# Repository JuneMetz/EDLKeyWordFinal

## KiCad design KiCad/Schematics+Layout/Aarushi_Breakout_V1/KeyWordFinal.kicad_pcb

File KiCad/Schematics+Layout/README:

Main Board Version 1 (MCP1642 Op AMP)

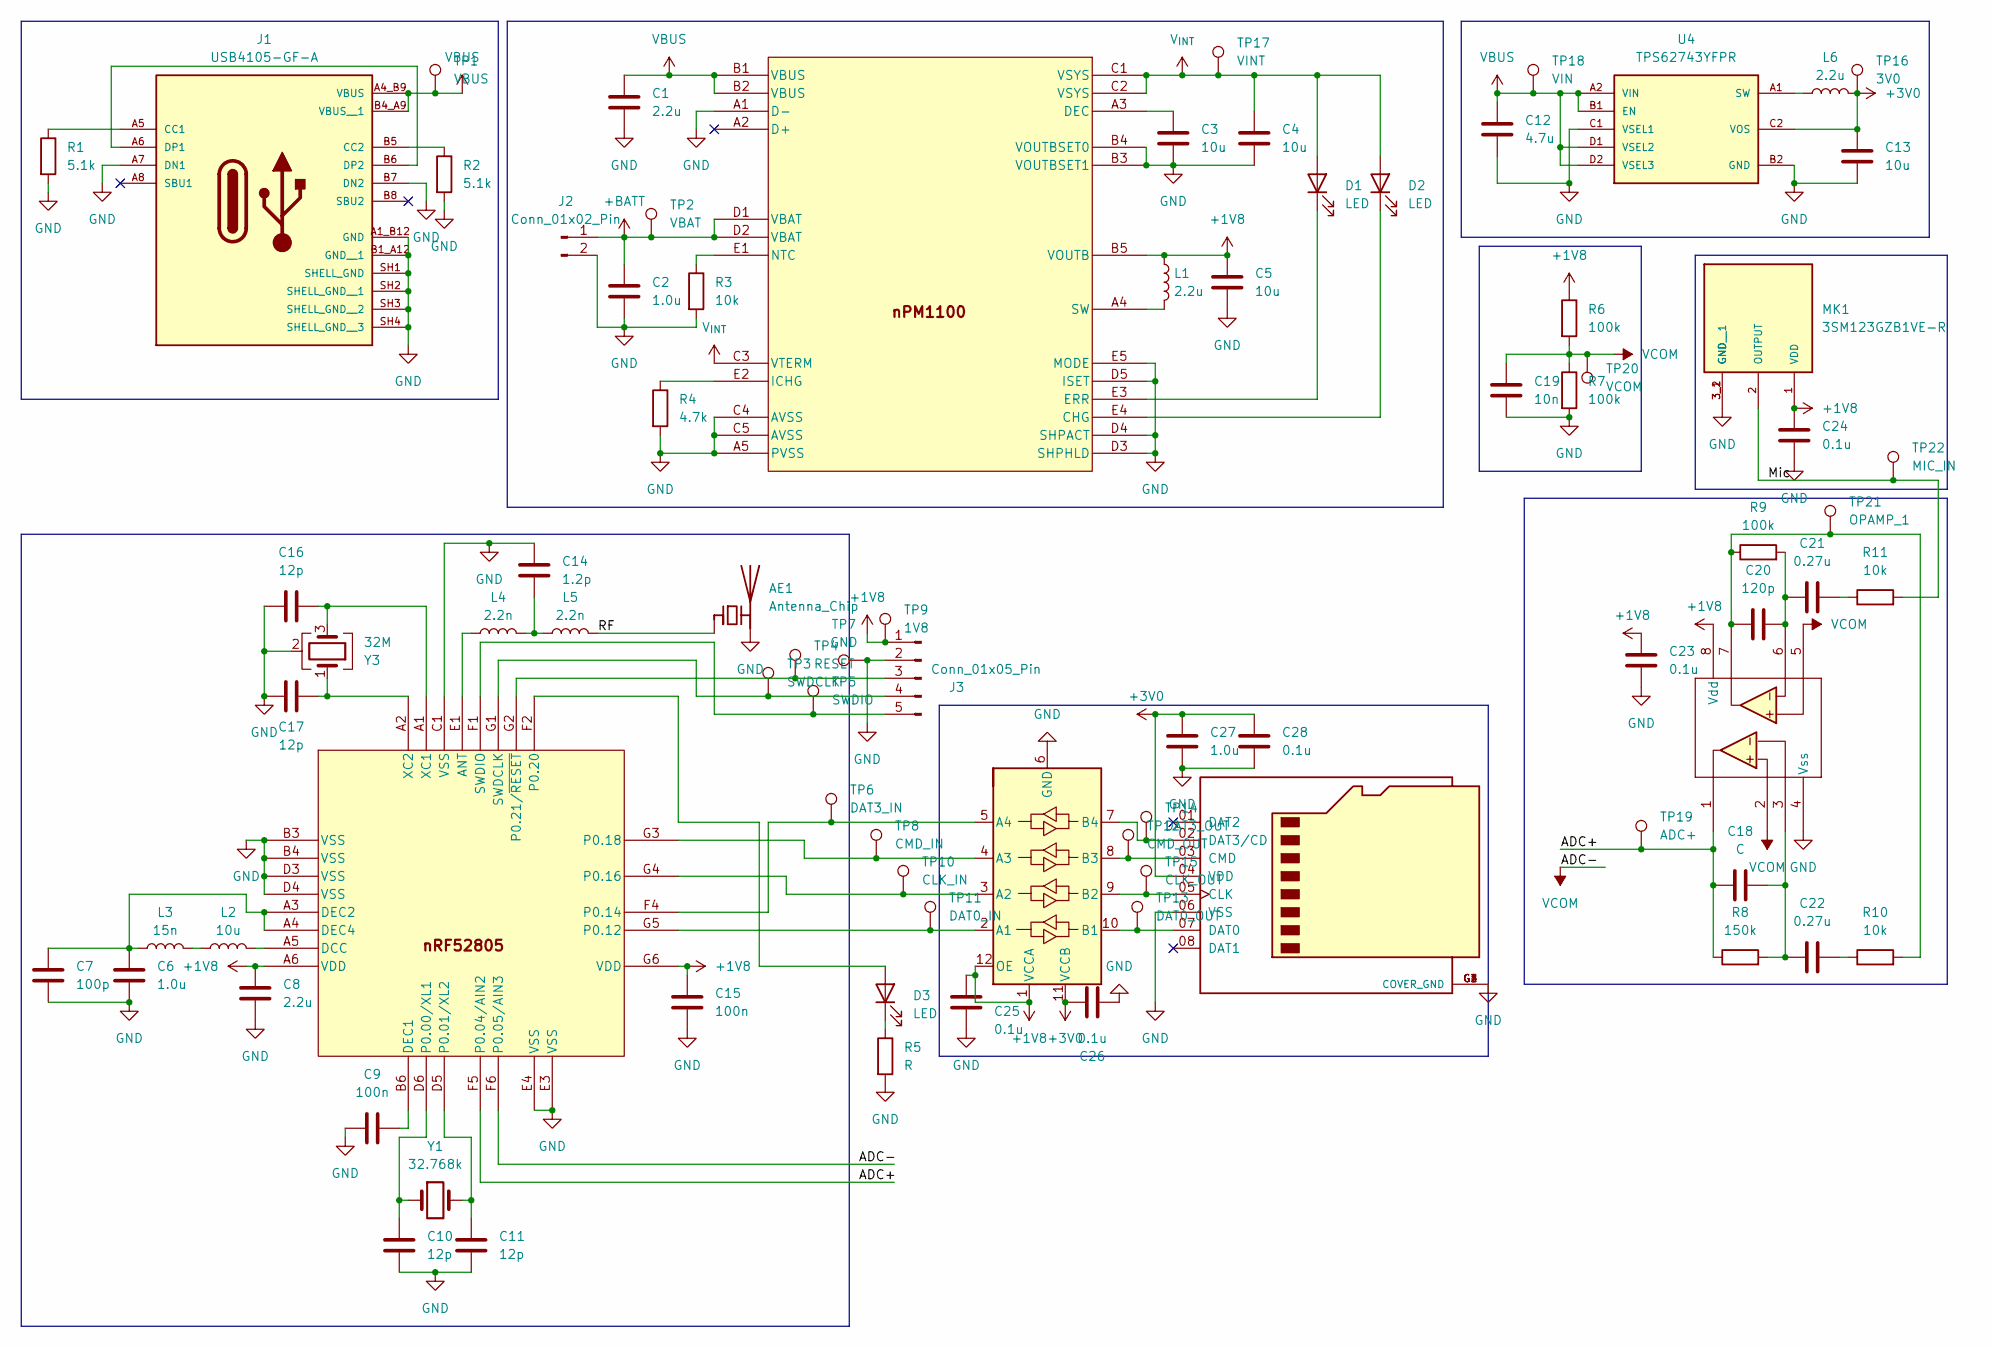
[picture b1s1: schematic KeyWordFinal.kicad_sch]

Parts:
AE1: Antenna_Chip; Texas_SWRA117D_2.4GHz_Left
C1: 2.2u; C_0603_1608Metric
C2: 1.0u; C_0201_0603Metric
C3, C4, C5, C13: 10u; C_0603_1608Metric
C6: 1.0u; C_0402_1005Metric
C7: 100p; C_0201_0603Metric
C8: 2.2u; C_0402_1005Metric
C9, C15: 100n; C_0201_0603Metric
C10, C11, C16, C17: 12p; C_0201_0603Metric
C12: 4.7u; C_0603_1608Metric
C14: 1.2p; C_0201_0603Metric
C18: C; C_0603_1608Metric
C19: 10n; C_0603_1608Metric
C20: 120p; C_0603_1608Metric
C21, C22: 0.27u; C_0603_1608Metric
C23, C24, C25, C26, C28: 0.1u; C_0603_1608Metric
C27: 1.0u; C_0603_1608Metric
D1, D2, D3: LED; LED_0603_1608Metric
J1: USB4105-GF-A; USB4105; PARTREV B4
J2: Conn_01x02_Pin; PinSocket_1x02_P2.54mm_Vertical
J3: Conn_01x05_Pin; PinSocket_1x05_P2.54mm_Vertical
J4: MSD-10-C; PARTREV 1.0
L1, L6: 2.2u; L_0805_2012Metric
L2: 10u; L_0603_1608Metric
L3: 15n; L_0402_1005Metric
L4, L5: 2.2n; L_0201_0603Metric
MK1: 3SM123GZB1VE-R; MIC_3SM123GZB1VE-R; PARTREV 1.4
R1, R2: 5.1k; R_0201_0603Metric
R3: 10k; R_0201_0603Metric
R4: 4.7k; R_0201_0603Metric
R5: R; R_0402_1005Metric
R6: 100k; R_0603_1608Metric
R7, R9: 100k; R_0402_1005Metric
R8: 150k; R_0402_1005Metric
R10, R11: 10k; R_0402_1005Metric
TP1: VBUS; TestPoint_Loop_D1.80mm_Drill1.0mm_Beaded
TP2: VBAT; TestPoint_Loop_D1.80mm_Drill1.0mm_Beaded
TP3: SWDCLK; TestPoint_Loop_D1.80mm_Drill1.0mm_Beaded
TP4: RESET; TestPoint_Loop_D1.80mm_Drill1.0mm_Beaded
TP5: SWDIO; TestPoint_Loop_D1.80mm_Drill1.0mm_Beaded
TP6: DAT3_IN; TestPoint_Loop_D1.80mm_Drill1.0mm_Beaded
TP7: GND; TestPoint_Loop_D1.80mm_Drill1.0mm_Beaded
TP8: CMD_IN; TestPoint_Loop_D1.80mm_Drill1.0mm_Beaded
TP9: 1V8; TestPoint_Loop_D1.80mm_Drill1.0mm_Beaded
TP10: CLK_IN; TestPoint_Loop_D1.80mm_Drill1.0mm_Beaded
TP11: DAT0_IN; TestPoint_Loop_D1.80mm_Drill1.0mm_Beaded
TP12: CMD_OUT; TestPoint_Loop_D1.80mm_Drill1.0mm_Beaded
TP13: DAT0_OUT; TestPoint_Loop_D1.80mm_Drill1.0mm_Beaded
TP14: DAT3_OUT; TestPoint_Loop_D1.80mm_Drill1.0mm_Beaded
TP15: CLK_OUT; TestPoint_Loop_D1.80mm_Drill1.0mm_Beaded
TP16: 3V0; TestPoint_Loop_D1.80mm_Drill1.0mm_Beaded
TP17: VINT; TestPoint_Loop_D1.80mm_Drill1.0mm_Beaded
TP18: VIN; TestPoint_Loop_D1.80mm_Drill1.0mm_Beaded
TP19: ADC+; TestPoint_Loop_D1.80mm_Drill1.0mm_Beaded
TP20: VCOM; TestPoint_Loop_D1.80mm_Drill1.0mm_Beaded
TP21: OPAMP_1; TestPoint_Loop_D1.80mm_Drill1.0mm_Beaded
TP22: MIC_IN; TestPoint_Loop_D1.80mm_Drill1.0mm_Beaded
U1: NRF52805-CAAA-R; NRF52805
U2: NPM1100-CAAA-R7; NPM1100
U3: TXB0104RUTR; TXB0104
U4: TPS62743YFPR; TPS62743
U5: MCP6142T-E/MS; MSOP-8_3x3mm_P0.65mm
Y1: 32.768k; Crystal_SMD_2012-2Pin_2.0x1.2mm
Y3: 32M; Crystal_SMD_2016-4Pin_2.0x1.6mm

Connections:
+1V8: C5.1, C8.1, C15.2, C23.2, C24.2, C25.2, J3.1, L1.1, MK1.1 (VDD), R6.1, TP9.1 (1_1), U1.A6 (VDD), U1.G6 (VDD), U2.B5 (VOUTB), U3.1 (VCCA), U3.12 (OE), U5.8 (Vdd)
+3V0: C13.1, C26.2, C27.1, C28.1, J4.04 (VDD), L6.2, TP16.1 (1_1), U3.11 (VCCB), U4.C2 (VOS)
/ADC+: C18.1, R8.1, TP19.1 (1_1), U1.F5 (P0.04/AIN2), U5.1
/Mic: MK1.2 (OUTPUT), R11.2, TP22.1 (1_1)
/RF: AE1.1 (FEED), L5.2
GND: AE1.2 (PCB_Trace), C1.2, C2.2, C3.2, C4.2, C5.2, C6.2, C7.2, C8.2, C9.1, C10.2, C11.2, C12.2, C13.2, C14.1, C15.1, C16.1, C17.1, C19.2, C23.1, C24.1, C25.1, C26.1, C27.2, C28.2, J1.A1_B12 (GND), J1.A7 (DN1), J1.B1_A12 (GND__1), J1.B7 (DN2), J1.SH1 (SHELL_GND), J1.SH2 (SHELL_GND__1), J1.SH3 (SHELL_GND__2), J1.SH4 (SHELL_GND__3), J2.2, J3.2, J4.06 (VSS), J4.G1 (COVER_GND), J4.G2 (COVER_GND), J4.G3 (COVER_GND), J4.G4 (COVER_GND), MK1.3_1 (GND), MK1.3_2 (GND__1), R1.2, R2.2, R3.2, R4.2, R5.2, R7.2, TP7.1 (1_1), U1.B3 (VSS), U1.B4 (VSS), U1.C1 (VSS), U1.D3 (VSS), U1.D4 (VSS), U1.E3 (VSS), U1.E4 (VSS), U2.A1 (D-), U2.A5 (PVSS), U2.B3 (VOUTBSET1), U2.B4 (VOUTBSET0), U2.C4 (AVSS), U2.C5 (AVSS), U2.D3 (SHPHLD), U2.D4 (SHPACT), U2.D5 (ISET), U2.E5 (MODE), U3.6 (GND), U4.B2 (GND), U4.C1 (VSEL1), U5.4 (Vss), Y3.2 (G), Y3.4 (G); also elsewhere on the board
unnamed: C14.2, L4.2, L5.1
unnamed: C18.2, C22.1, R8.2, U5.3
unnamed: C20.1, R9.1, R10.2, TP21.1 (1_1), U5.7
unnamed: C20.2, C21.1, R9.2, U5.6
unnamed: C21.2, R11.1
unnamed: C22.2, R10.1
unnamed: D1.1 (K), U2.E3 (ERR)
unnamed: D2.1 (K), U2.E4 (CHG)
unnamed: D3.2 (A), U1.F2 (P0.20)
unnamed: D3.1 (K), R5.1
unnamed: J1.A5 (CC1), R1.1
unnamed: J1.B5 (CC2), R2.1
unnamed: J1.A6 (DP1), J1.B6 (DP2)
unnamed: J3.3, TP4.1 (1_1), U1.G2 (P0.21/~RESET)
unnamed: J3.4, TP3.1 (1_1), U1.G1 (SWDCLK)
unnamed: J3.5, TP5.1 (1_1), U1.F1 (SWDIO)
unnamed: J4.05 (CLK), TP15.1 (1_1), U3.9 (B2)
unnamed: J4.03 (CMD), TP12.1 (1_1), U3.8 (B3)
unnamed: J4.07 (DAT0), TP13.1 (1_1), U3.10 (B1)
unnamed: J4.02 (DAT3/CD), TP14.1 (1_1), U3.7 (B4)
unnamed: L2.1, L3.2
unnamed: L4.1, U1.E1 (ANT)
unnamed: L2.2, U1.A5 (DCC)
unnamed: C9.2, U1.B6 (DEC1)
unnamed: C6.1, C7.1, L3.1, U1.A3 (DEC2), U1.A4 (DEC4)
unnamed: C10.1, U1.D6 (P0.00/XL1), Y1.1
unnamed: C11.1, U1.D5 (P0.01/XL2), Y1.2
unnamed: TP11.1 (1_1), U1.G5 (P0.12), U3.2 (A1)
unnamed: TP6.1 (1_1), U1.F4 (P0.14), U3.5 (A4)
unnamed: TP10.1 (1_1), U1.G4 (P0.16), U3.3 (A2)
unnamed: TP8.1 (1_1), U1.G3 (P0.18), U3.4 (A3)
unnamed: C16.2, U1.A1 (XC1), Y3.3
unnamed: C17.2, U1.A2 (XC2), Y3.1
unnamed: C3.1, U2.A3 (DEC)
unnamed: R4.1, U2.E2 (ICHG)
unnamed: R3.1, U2.E1 (NTC)
unnamed: L1.2, U2.A4 (SW)
unnamed: L6.1, U4.A1 (SW)
VCOM: C19.1, R6.2, R7.1, TP20.1 (1_1), U1.F6 (P0.05/AIN3), U5.2, U5.5
V_{INT}: C4.1, D1.2 (A), D2.2 (A), TP17.1 (1_1), U2.C1 (VSYS), U2.C2 (VSYS), U2.C3 (VTERM)

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
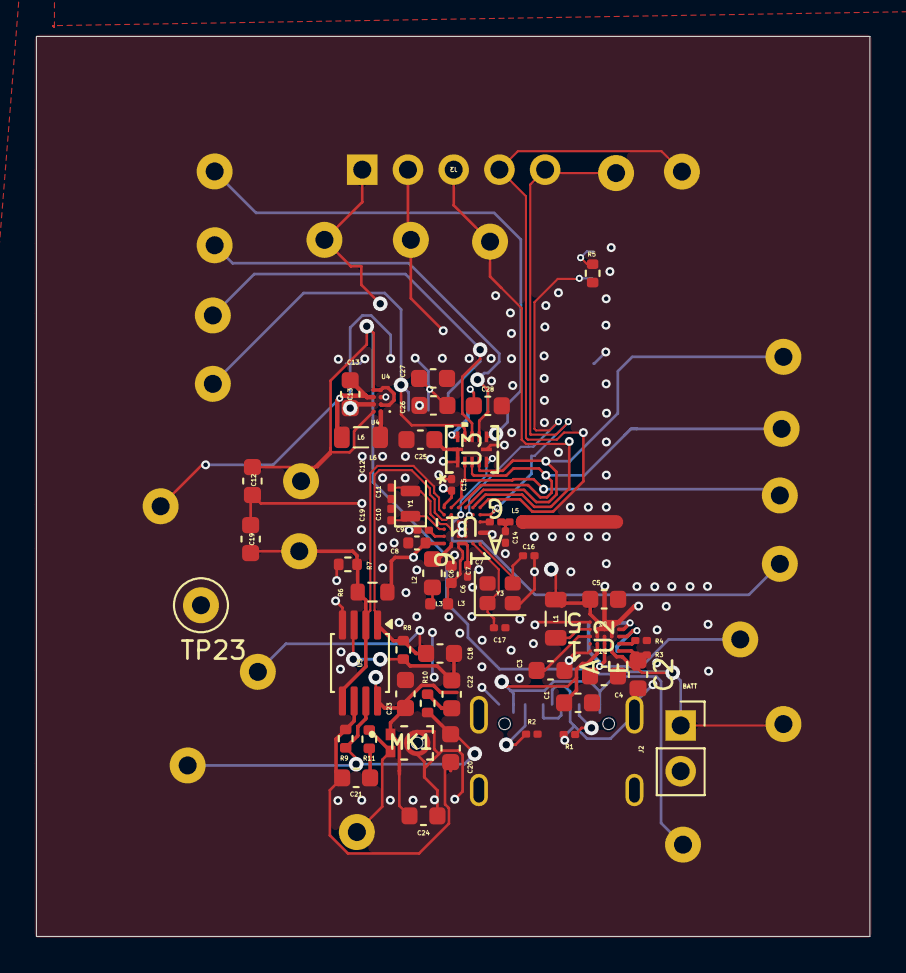
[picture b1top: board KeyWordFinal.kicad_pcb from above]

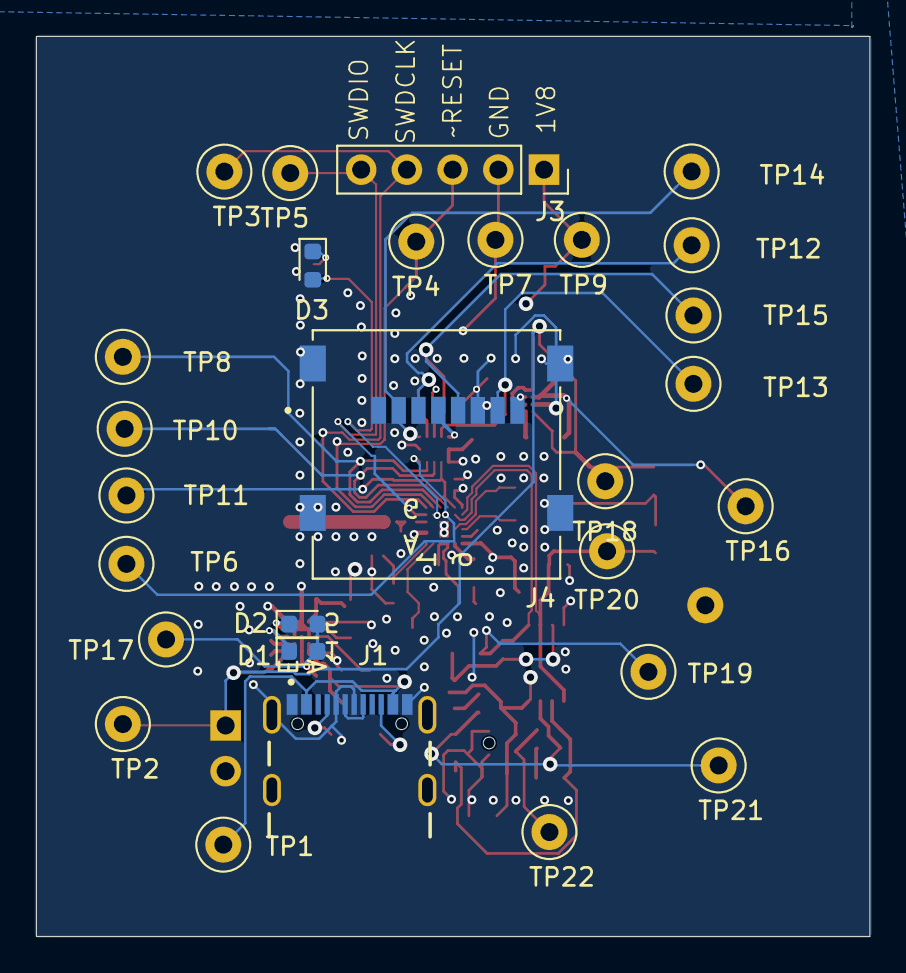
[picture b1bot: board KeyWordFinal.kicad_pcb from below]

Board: 2 copper layers, 46.3 x 50.0 mm, 83 parts (28 on the bottom side), 47 nets.

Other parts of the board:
TP23: GND; TestPoint_Loop_D1.80mm_Drill1.0mm_Beaded

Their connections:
GND: TP23.1 (1_1); also elsewhere on the board

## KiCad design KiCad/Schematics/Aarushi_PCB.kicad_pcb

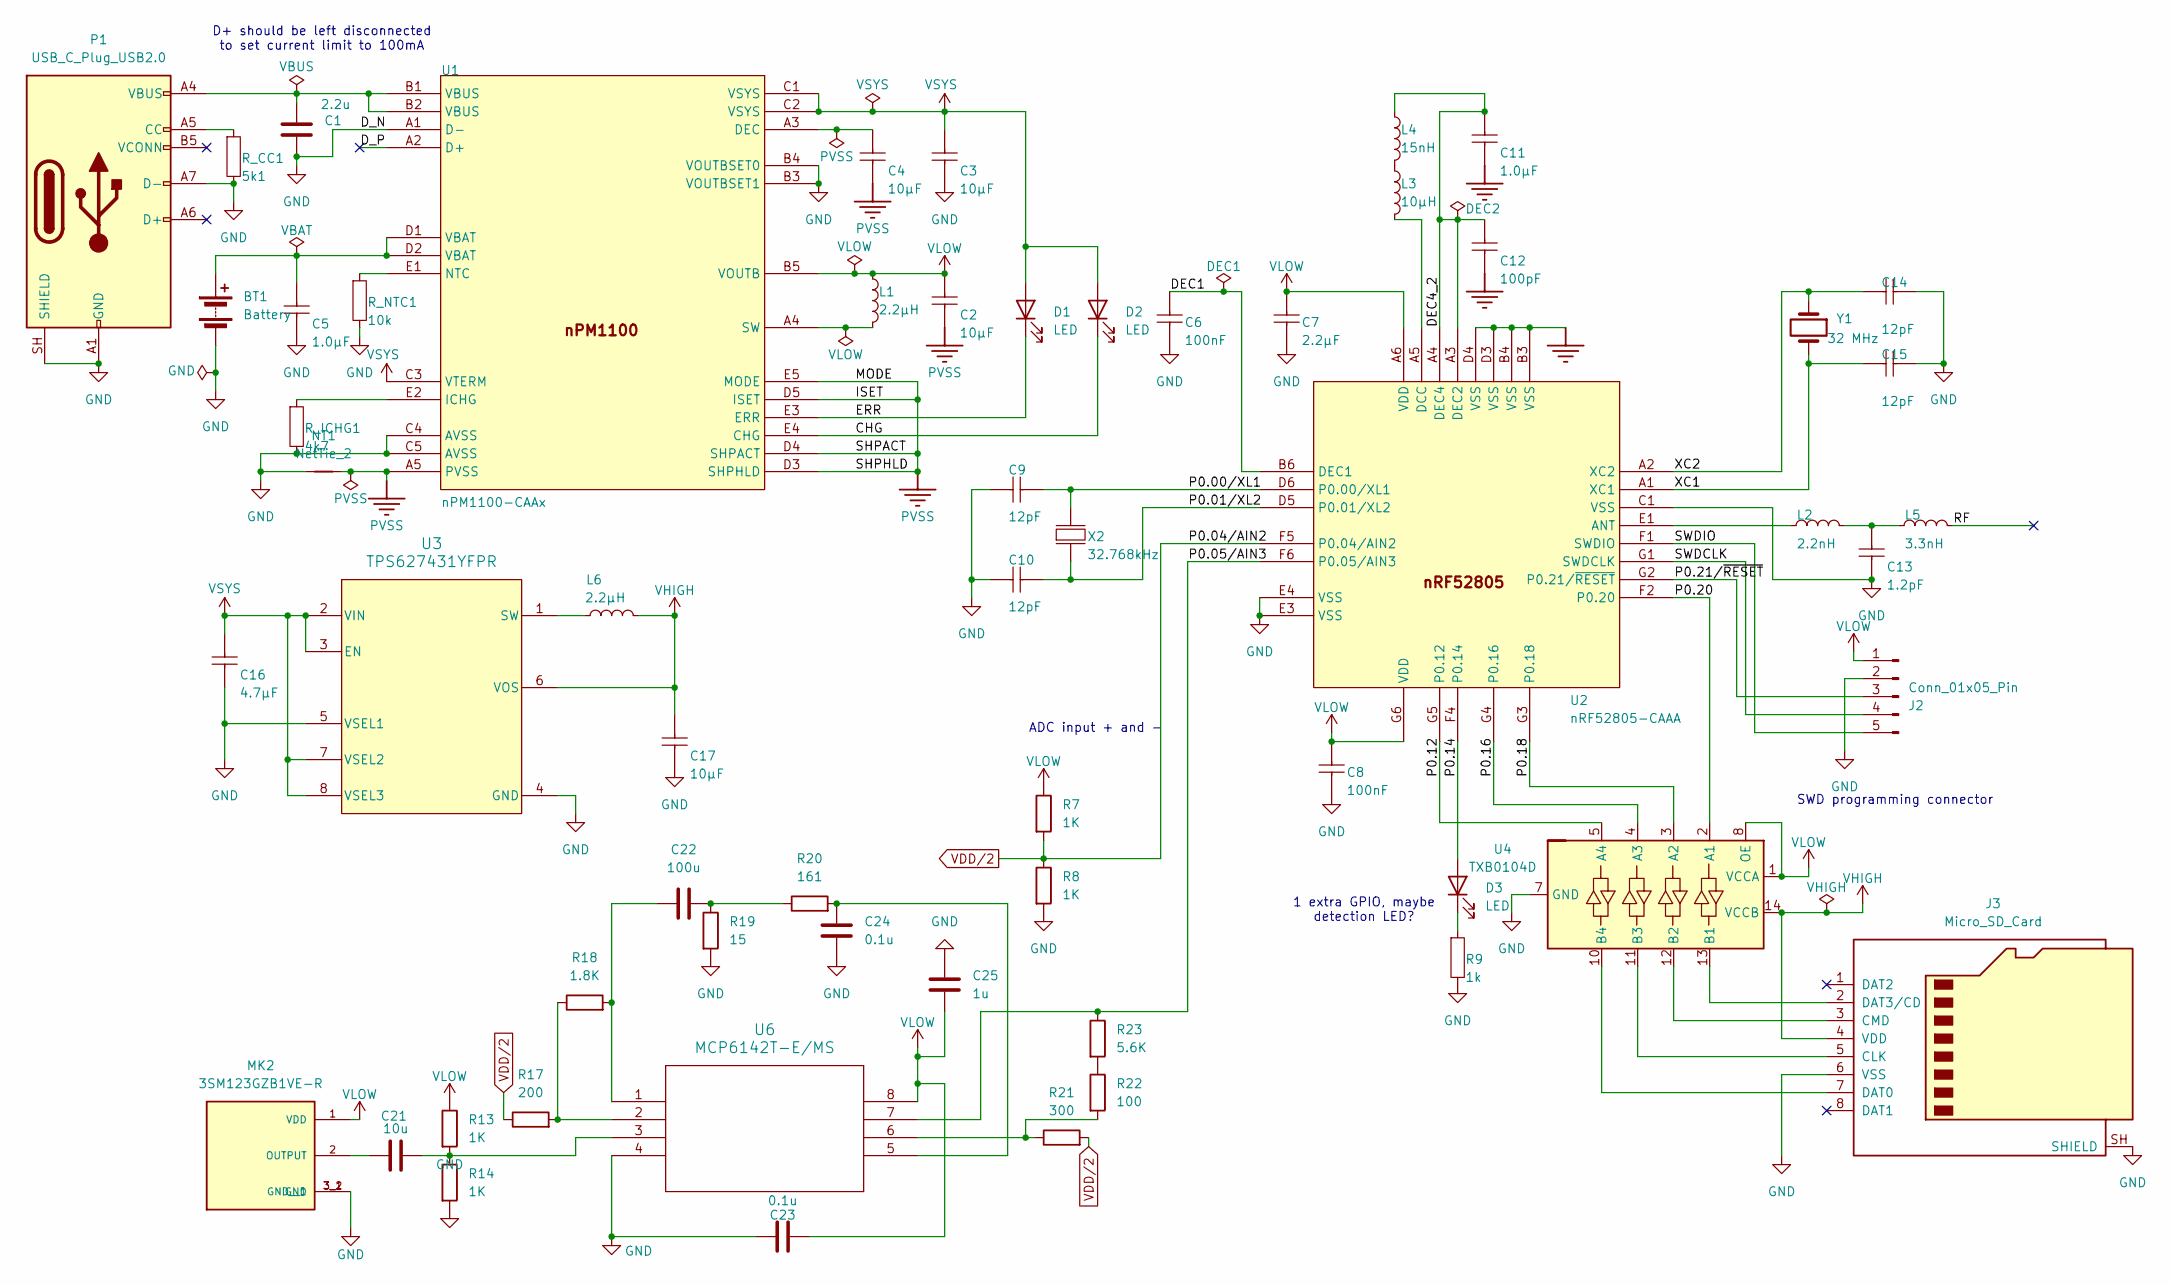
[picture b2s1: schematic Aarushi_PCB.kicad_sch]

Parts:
BT1: Battery; BatteryHolder_Keystone_103_1x20mm
C1: 2.2u; C_1808_4520Metric_Pad1.72x2.30mm_HandSolder
C2, C3, C4, C17: 10µF; C_1808_4520Metric_Pad1.72x2.30mm_HandSolder
C5: 1.0µF; C_1808_4520Metric_Pad1.72x2.30mm_HandSolder
C6, C8: 100nF; C_1808_4520Metric_Pad1.72x2.30mm_HandSolder; PART NUMBER C0201-100n
C7: 2.2µF; C_1808_4520Metric_Pad1.72x2.30mm_HandSolder; PART NUMBER C0402-2µ2
C9, C10, C14, C15: 12pF; C_1808_4520Metric_Pad1.72x2.30mm_HandSolder; PART NUMBER C0201-12p
C11: 1.0µF; C_1808_4520Metric_Pad1.72x2.30mm_HandSolder; PART NUMBER C0402-1µ0
C12: 100pF; C_1808_4520Metric_Pad1.72x2.30mm_HandSolder; PART NUMBER C0201-100p
C13: 1.2pF; C_1808_4520Metric_Pad1.72x2.30mm_HandSolder; PART NUMBER C0201-1.2p
C16: 4.7µF; C_1808_4520Metric_Pad1.72x2.30mm_HandSolder
C21: 10u; C_1808_4520Metric_Pad1.72x2.30mm_HandSolder
C22: 100u; C_1808_4520Metric_Pad1.72x2.30mm_HandSolder
C23, C24: 0.1u; C_1808_4520Metric_Pad1.72x2.30mm_HandSolder
C25: 1u; C_1808_4520Metric_Pad1.72x2.30mm_HandSolder
D1, D2, D3: LED; LED_0201_0603Metric_Pad0.64x0.40mm_HandSolder
J2: Conn_01x05_Pin; JST_EH_B5B-EH-A_1x05_P2.50mm_Vertical
J3: Micro_SD_Card; microSD_HC_Molex_47219-2001
L1, L6: 2.2µH; L_6.3x6.3_H3
L2: 2.2nH; L_6.3x6.3_H3; PART NUMBER L0201-2n2
L3: 10µH; L_6.3x6.3_H3; PART NUMBER L0603-10µ
L4: 15nH; L_6.3x6.3_H3; PART NUMBER L0402-15n
L5: 3.3nH; L_6.3x6.3_H3; PART NUMBER L0201-3n3
MK2: 3SM123GZB1VE-R; MIC_3SM123GZB1VE-R; PARTREV 1.4
NT1: NetTie_2; NetTie-2_SMD_Pad2.0mm
P1: USB_C_Plug_USB2.0; USB_C_Plug_JAE_DX07P024AJ1
R7, R8, R13, R14: 1K; R_4020_10251Metric_Pad1.65x5.30mm_HandSolder
R9: 1k; R_4020_10251Metric_Pad1.65x5.30mm_HandSolder
R17: 200; R_4020_10251Metric_Pad1.65x5.30mm_HandSolder
R18: 1.8K; R_4020_10251Metric_Pad1.65x5.30mm_HandSolder
R19: 15; R_4020_10251Metric_Pad1.65x5.30mm_HandSolder
R20: 161; R_4020_10251Metric_Pad1.65x5.30mm_HandSolder
R21: 300; R_4020_10251Metric_Pad1.65x5.30mm_HandSolder
R22: 100; R_4020_10251Metric_Pad1.65x5.30mm_HandSolder
R23: 5.6K; R_4020_10251Metric_Pad1.65x5.30mm_HandSolder
R_CC1: 5k1; R_4020_10251Metric_Pad1.65x5.30mm_HandSolder
R_ICHG1: 4k7; R_4020_10251Metric_Pad1.65x5.30mm_HandSolder
R_NTC1: 10k; R_4020_10251Metric_Pad1.65x5.30mm_HandSolder
U1: nPM1100-CAAx; WLCSP_2p075X2p075_NOR
U2: nRF52805-CAAA; WLCSP28_2p482x2p464_nRF52805_NOR; PART NUMBER nRF52805-CAAA
U3: TPS627431YFPR; YFP0008-C01-IPC_A
U4: TXB0104D; SOIC-14_3.9x8.7mm_P1.27mm
U6: MCP6142T-E/MS; MSOP8_MC_MCH
X2: 32.768kHz; Oscillator_SMD_Abracon_ASCO-4Pin_1.6x1.2mm; PART NUMBER XTAL_SMD2012_32.768kHz_9pF_General
Y1: 32 MHz; Oscillator_SMD_Abracon_ASCO-4Pin_1.6x1.2mm

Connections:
/CHG: D2.1 (K), U1.E4 (CHG)
/DEC1: C6.1, U2.B6 (DEC1)
/DEC4_2: C11.2, C12.2, L4.1, U2.A3 (DEC2), U2.A4 (DEC4)
/D_P: U1.A2 (D+)
/ERR: D1.1 (K), U1.E3 (ERR)
/P0.00/XL1: C9.2, U2.D6 (P0.00/XL1), X2.1 (inp)
/P0.01/XL2: C10.2, U2.D5 (P0.01/XL2), X2.2 (out)
/P0.05/AIN3: R23.1, U2.F6 (P0.05/AIN3), U6.7
/P0.12: U2.G5 (P0.12), U4.5 (A4)
/P0.14: D3.2 (A), U2.F4 (P0.14)
/P0.16: U2.G4 (P0.16), U4.4 (A3)
/P0.18: U2.G3 (P0.18), U4.3 (A2)
/P0.20: U2.F2 (P0.20), U4.2 (A1)
/P0.21/~RESET: J2.3, U2.G2 (P0.21/~RESET)
/RF: L5.2
/SWDCLK: J2.4, U2.G1 (SWDCLK)
/SWDIO: J2.5, U2.F1 (SWDIO)
/XC1: C15.2, U2.A1 (XC1), Y1.2
/XC2: C14.2, U2.A2 (XC2), Y1.1
GND: BT1.2 (-), C1.1, C3.1, C5.1, C6.2, C7.2, C8.2, C9.1, C10.1, C11.1, C12.1, C13.1, C14.1, C15.1, C16.1, C17.1, C23.2, C24.2, C25.2, J2.2, J3.6 (VSS), J3.SH (SHIELD), MK2.3_1 (GND), MK2.3_2 (GND__1), NT1.1, P1.A1 (GND), P1.A7 (D-), P1.A12 (GND), P1.B1 (GND), P1.B12 (GND), P1.SH (SHIELD), R8.2, R9.1, R14.2, R19.2, R_CC1.1, R_ICHG1.1, R_NTC1.1, U1.A1 (D-), U1.B3 (VOUTBSET1), U1.B4 (VOUTBSET0), U1.C4 (AVSS), U1.C5 (AVSS), U2.B3 (VSS), U2.B4 (VSS), U2.C1 (VSS), U2.D3 (VSS), U2.D4 (VSS), U2.E3 (VSS), U2.E4 (VSS), U3.4 (GND), U3.5 (VSEL1), U4.7 (GND), U6.4
unnamed: BT1.1 (+), C5.2, U1.D1 (VBAT), U1.D2 (VBAT)
unnamed: C1.2, P1.A4 (VBUS), P1.A9 (VBUS), P1.B4 (VBUS), P1.B9 (VBUS), U1.B1 (VBUS), U1.B2 (VBUS)
unnamed: C13.2, L2.2, L5.1
unnamed: C21.2, R13.2, R14.1, U6.3
unnamed: C22.1, R18.2, U6.1
unnamed: C22.2, R19.1, R20.1
unnamed: C24.1, R20.2, U6.5
unnamed: D3.1 (K), R9.2
unnamed: J3.5 (CLK), U4.11 (B3)
unnamed: J3.3 (CMD), U4.12 (B2)
unnamed: J3.7 (DAT0), U4.10 (B4)
unnamed: J3.2 (DAT3/CD), U4.13 (B1)
unnamed: L3.1, L4.2
unnamed: C21.1, MK2.2 (OUTPUT)
unnamed: P1.A5 (CC), R_CC1.2
unnamed: R17.2, R18.1, U6.2
unnamed: R21.1, R22.2, U6.6
unnamed: R22.1, R23.2
unnamed: C4.2, U1.A3 (DEC)
unnamed: R_ICHG1.2, U1.E2 (ICHG)
unnamed: R_NTC1.2, U1.E1 (NTC)
unnamed: L1.2, U1.A4 (SW)
unnamed: L2.1, U2.E1 (ANT)
unnamed: L3.2, U2.A5 (DCC)
unnamed: L6.1, U3.1 (SW)
PVSS: C2.1, C4.1, NT1.2, U1.A5 (PVSS), U1.D3 (SHPHLD), U1.D4 (SHPACT), U1.D5 (ISET), U1.E5 (MODE)
VDD/2: R7.2, R8.1, R17.1, R21.2, U2.F5 (P0.04/AIN2)
VHIGH: C17.2, J3.4 (VDD), L6.2, U3.6 (VOS), U4.14 (VCCB)
VLOW: C2.2, C7.1, C8.1, C23.1, C25.1, J2.1, L1.1, MK2.1 (VDD), R7.1, R13.1, U1.B5 (VOUTB), U2.A6 (VDD), U2.G6 (VDD), U4.1 (VCCA), U4.8 (OE), U6.8
VSYS: C3.2, C16.2, D1.2 (A), D2.2 (A), U1.C1 (VSYS), U1.C2 (VSYS), U1.C3 (VTERM), U3.2 (VIN), U3.3 (EN), U3.7 (VSEL2), U3.8 (VSEL3)

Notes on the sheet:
SWD programming connector
ADC input + and -
D+ should be left disconnected to set current limit to 100mA
1 extra GPIO, maybe detection LED?

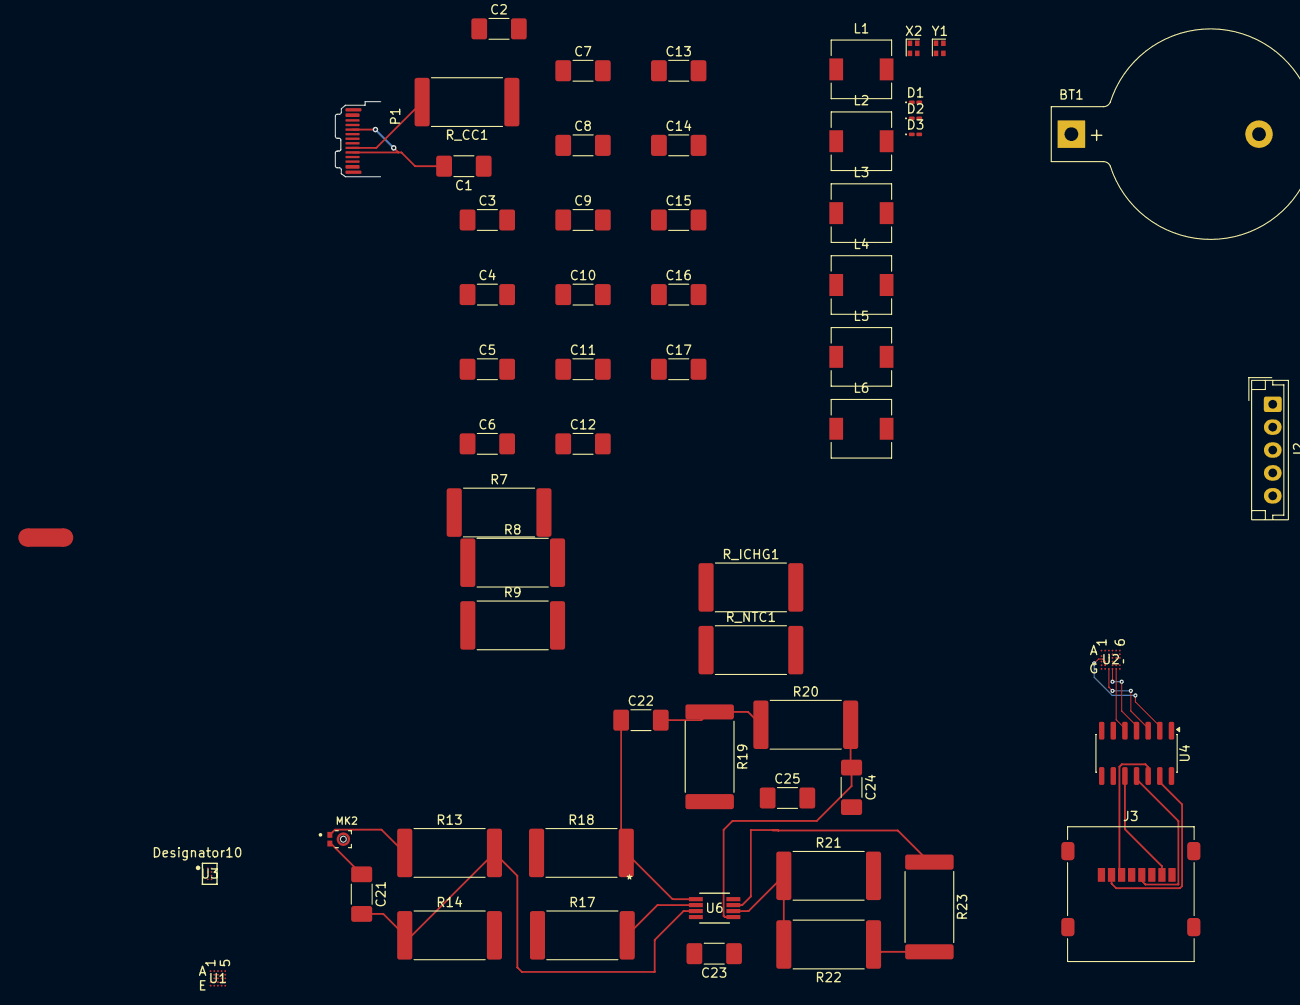
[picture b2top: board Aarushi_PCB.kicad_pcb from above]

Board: 2 copper layers, 59 parts (0 on the bottom side), 48 nets.
